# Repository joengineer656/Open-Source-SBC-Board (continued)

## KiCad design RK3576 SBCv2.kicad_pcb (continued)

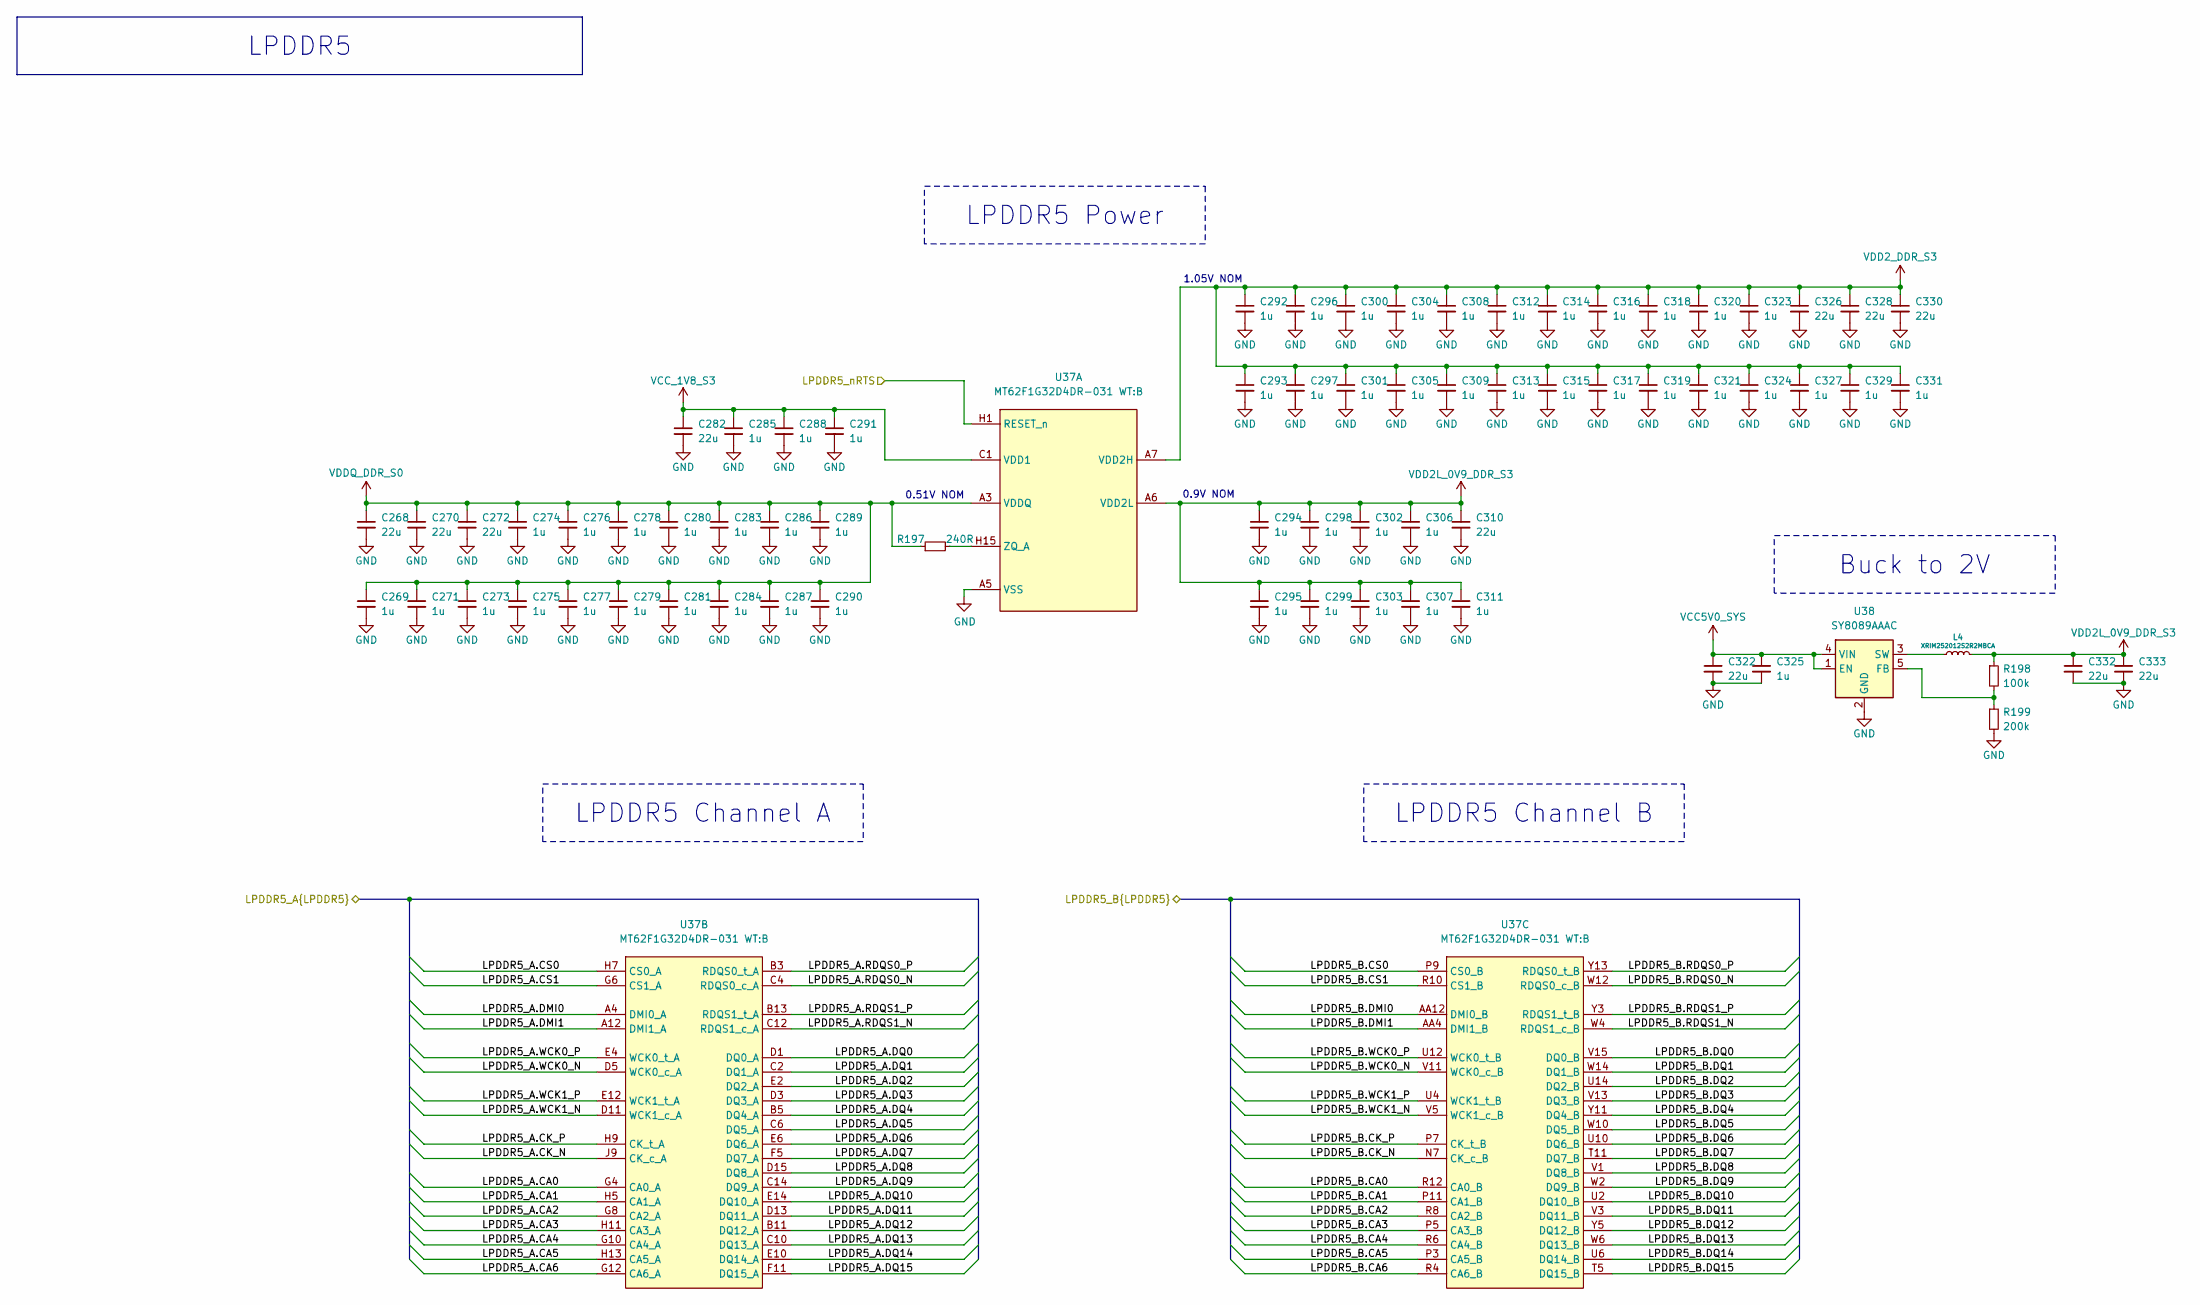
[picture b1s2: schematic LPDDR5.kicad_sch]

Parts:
C268, C270, C272, C282, C310, C322, C326, C328, C330, C332, C333: 22u; C_0603_1608Metric; Mouser Part CL10A226MP8NUNE; LCSC Part C86295
C269, C271, C273, C274, C275, C276, C277, C278, C279, C280, C281, C283, C284, C285, C286, C287, C288, C289, C290, C291, C292, C293, C294, C295, C296, C297, C298, C299, C300, C301, C302, C303, C304, C305, C306, C307, C308, C309, C311, C312, C313, C314, C315, C316, C317, C318, C319, C320, C321, C323, C324, C325, C327, C329, C331: 1u; C_0201_0603Metric_Pad0.64x0.40mm_HandSolder; Mouser Part CL03A105KP3NSNC; LCSC Part C5209398
L4: XRIM252012S2R2MBCA; L_1008_2520Metric; LCSC Part C22471111
R197: 240R; R_0402_1005Metric; Mouser Part 603-RC0402FR-07240RL; LCSC Part C114755
R198: 100k; R_0402_1005Metric; Mouser Part 603-RC0402FR-0710KL; LCSC Part C60490
R199: 200k; R_0402_1005Metric; Mouser Part 603-RC0402FR-0710KL; LCSC Part C60490
U37: MT62F1G32D4DR-031 WT:B; LPDDR5 BGA 315; MPN MT62F1G32D4DR-031 WT:B; Mouser Part 340-450481-TRAY
U38: SY8089AAAC; SOT-23-5; LCSC Part C78988

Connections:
/LPDDR5/LPDDR5_A.CA0: U37.G4 (CA0_A); also elsewhere on the board
/LPDDR5/LPDDR5_A.CA1: U37.H5 (CA1_A); also elsewhere on the board
/LPDDR5/LPDDR5_A.CA2: U37.G8 (CA2_A); also elsewhere on the board
/LPDDR5/LPDDR5_A.CA3: U37.H11 (CA3_A); also elsewhere on the board
/LPDDR5/LPDDR5_A.CA4: U37.G10 (CA4_A); also elsewhere on the board
/LPDDR5/LPDDR5_A.CA5: U37.H13 (CA5_A); also elsewhere on the board
/LPDDR5/LPDDR5_A.CA6: U37.G12 (CA6_A); also elsewhere on the board
/LPDDR5/LPDDR5_A.CK_N: U37.J9 (CK_c_A); also elsewhere on the board
/LPDDR5/LPDDR5_A.CK_P: U37.H9 (CK_t_A); also elsewhere on the board
/LPDDR5/LPDDR5_A.CS0: U37.H7 (CS0_A); also elsewhere on the board
/LPDDR5/LPDDR5_A.CS1: U37.G6 (CS1_A); also elsewhere on the board
/LPDDR5/LPDDR5_A.DMI0: U37.A4 (DMI0_A); also elsewhere on the board
/LPDDR5/LPDDR5_A.DMI1: U37.A12 (DMI1_A); also elsewhere on the board
/LPDDR5/LPDDR5_A.DQ0: U37.D1 (DQ0_A); also elsewhere on the board
/LPDDR5/LPDDR5_A.DQ1: U37.C2 (DQ1_A); also elsewhere on the board
/LPDDR5/LPDDR5_A.DQ2: U37.E2 (DQ2_A); also elsewhere on the board
/LPDDR5/LPDDR5_A.DQ3: U37.D3 (DQ3_A); also elsewhere on the board
/LPDDR5/LPDDR5_A.DQ4: U37.B5 (DQ4_A); also elsewhere on the board
/LPDDR5/LPDDR5_A.DQ5: U37.C6 (DQ5_A); also elsewhere on the board
/LPDDR5/LPDDR5_A.DQ6: U37.E6 (DQ6_A); also elsewhere on the board
/LPDDR5/LPDDR5_A.DQ7: U37.F5 (DQ7_A); also elsewhere on the board
/LPDDR5/LPDDR5_A.DQ8: U37.D15 (DQ8_A); also elsewhere on the board
/LPDDR5/LPDDR5_A.DQ9: U37.C14 (DQ9_A); also elsewhere on the board
/LPDDR5/LPDDR5_A.DQ10: U37.E14 (DQ10_A); also elsewhere on the board
/LPDDR5/LPDDR5_A.DQ11: U37.D13 (DQ11_A); also elsewhere on the board
/LPDDR5/LPDDR5_A.DQ12: U37.B11 (DQ12_A); also elsewhere on the board
/LPDDR5/LPDDR5_A.DQ13: U37.C10 (DQ13_A); also elsewhere on the board
/LPDDR5/LPDDR5_A.DQ14: U37.E10 (DQ14_A); also elsewhere on the board
/LPDDR5/LPDDR5_A.DQ15: U37.F11 (DQ15_A); also elsewhere on the board
/LPDDR5/LPDDR5_A.RDQS0_N: U37.C4 (RDQS0_c_A); also elsewhere on the board
/LPDDR5/LPDDR5_A.RDQS0_P: U37.B3 (RDQS0_t_A); also elsewhere on the board
/LPDDR5/LPDDR5_A.RDQS1_N: U37.C12 (RDQS1_c_A); also elsewhere on the board
/LPDDR5/LPDDR5_A.RDQS1_P: U37.B13 (RDQS1_t_A); also elsewhere on the board
/LPDDR5/LPDDR5_A.WCK0_N: U37.D5 (WCK0_c_A); also elsewhere on the board
/LPDDR5/LPDDR5_A.WCK0_P: U37.E4 (WCK0_t_A); also elsewhere on the board
/LPDDR5/LPDDR5_A.WCK1_N: U37.D11 (WCK1_c_A); also elsewhere on the board
/LPDDR5/LPDDR5_A.WCK1_P: U37.E12 (WCK1_t_A); also elsewhere on the board
/LPDDR5/LPDDR5_B.CA0: U37.R12 (CA0_B); also elsewhere on the board
/LPDDR5/LPDDR5_B.CA1: U37.P11 (CA1_B); also elsewhere on the board
/LPDDR5/LPDDR5_B.CA2: U37.R8 (CA2_B); also elsewhere on the board
/LPDDR5/LPDDR5_B.CA3: U37.P5 (CA3_B); also elsewhere on the board
/LPDDR5/LPDDR5_B.CA4: U37.R6 (CA4_B); also elsewhere on the board
/LPDDR5/LPDDR5_B.CA5: U37.P3 (CA5_B); also elsewhere on the board
/LPDDR5/LPDDR5_B.CA6: U37.R4 (CA6_B); also elsewhere on the board
/LPDDR5/LPDDR5_B.CK_N: U37.N7 (CK_c_B); also elsewhere on the board
/LPDDR5/LPDDR5_B.CK_P: U37.P7 (CK_t_B); also elsewhere on the board
/LPDDR5/LPDDR5_B.CS0: U37.P9 (CS0_B); also elsewhere on the board
/LPDDR5/LPDDR5_B.CS1: U37.R10 (CS1_B); also elsewhere on the board
/LPDDR5/LPDDR5_B.DMI0: U37.AA12 (DMI0_B); also elsewhere on the board
/LPDDR5/LPDDR5_B.DMI1: U37.AA4 (DMI1_B); also elsewhere on the board
/LPDDR5/LPDDR5_B.DQ0: U37.V15 (DQ0_B); also elsewhere on the board
/LPDDR5/LPDDR5_B.DQ1: U37.W14 (DQ1_B); also elsewhere on the board
/LPDDR5/LPDDR5_B.DQ2: U37.U14 (DQ2_B); also elsewhere on the board
/LPDDR5/LPDDR5_B.DQ3: U37.V13 (DQ3_B); also elsewhere on the board
/LPDDR5/LPDDR5_B.DQ4: U37.Y11 (DQ4_B); also elsewhere on the board
/LPDDR5/LPDDR5_B.DQ5: U37.W10 (DQ5_B); also elsewhere on the board
/LPDDR5/LPDDR5_B.DQ6: U37.U10 (DQ6_B); also elsewhere on the board
/LPDDR5/LPDDR5_B.DQ7: U37.T11 (DQ7_B); also elsewhere on the board
/LPDDR5/LPDDR5_B.DQ8: U37.V1 (DQ8_B); also elsewhere on the board
/LPDDR5/LPDDR5_B.DQ9: U37.W2 (DQ9_B); also elsewhere on the board
/LPDDR5/LPDDR5_B.DQ10: U37.U2 (DQ10_B); also elsewhere on the board
/LPDDR5/LPDDR5_B.DQ11: U37.V3 (DQ11_B); also elsewhere on the board
/LPDDR5/LPDDR5_B.DQ12: U37.Y5 (DQ12_B); also elsewhere on the board
/LPDDR5/LPDDR5_B.DQ13: U37.W6 (DQ13_B); also elsewhere on the board
/LPDDR5/LPDDR5_B.DQ14: U37.U6 (DQ14_B); also elsewhere on the board
/LPDDR5/LPDDR5_B.DQ15: U37.T5 (DQ15_B); also elsewhere on the board
/LPDDR5/LPDDR5_B.RDQS0_N: U37.W12 (RDQS0_c_B); also elsewhere on the board
/LPDDR5/LPDDR5_B.RDQS0_P: U37.Y13 (RDQS0_t_B); also elsewhere on the board
/LPDDR5/LPDDR5_B.RDQS1_N: U37.W4 (RDQS1_c_B); also elsewhere on the board
/LPDDR5/LPDDR5_B.RDQS1_P: U37.Y3 (RDQS1_t_B); also elsewhere on the board
/LPDDR5/LPDDR5_B.WCK0_N: U37.V11 (WCK0_c_B); also elsewhere on the board
/LPDDR5/LPDDR5_B.WCK0_P: U37.U12 (WCK0_t_B); also elsewhere on the board
/LPDDR5/LPDDR5_B.WCK1_N: U37.V5 (WCK1_c_B); also elsewhere on the board
/LPDDR5/LPDDR5_B.WCK1_P: U37.U4 (WCK1_t_B); also elsewhere on the board
/LPDDR5/LPDDR5_nRTS: U37.H1 (RESET_n); also elsewhere on the board
unnamed: L4.1, U38.3 (SW)
VDD2_DDR_S3: C292.1, C293.1, C296.1, C297.1, C300.1, C301.1, C304.1, C305.1, C308.1, C309.1, C312.1, C313.1, C314.1, C315.1, C316.1, C317.1, C318.1, C319.1, C320.1, C321.1, C323.1, C324.1, C326.1, C327.1, C328.1, C329.1, C330.1, C331.1, U37.A7 (VDD2H), U37.A8 (VDD2H), U37.A9 (VDD2H), U37.AA7 (VDD2H), U37.AA8 (VDD2H), U37.AA9 (VDD2H), U37.B7 (VDD2H), U37.B9 (VDD2H), U37.C7 (VDD2H), U37.C9 (VDD2H), U37.D8 (VDD2H), U37.E7 (VDD2H), U37.E9 (VDD2H), U37.F6 (VDD2H), U37.F7 (VDD2H), U37.F9 (VDD2H), U37.F10 (VDD2H), U37.J5 (VDD2H), U37.J11 (VDD2H), U37.K1 (VDD2H), U37.K2 (VDD2H), U37.K3 (VDD2H), U37.K4 (VDD2H), U37.K5 (VDD2H), U37.K6 (VDD2H), U37.K10 (VDD2H), U37.K11 (VDD2H), U37.K12 (VDD2H), U37.K13 (VDD2H), U37.K14 (VDD2H), U37.K15 (VDD2H), U37.L6 (VDD2H), U37.L7 (VDD2H), U37.L8 (VDD2H), U37.L9 (VDD2H), U37.L10 (VDD2H), U37.M1 (VDD2H), U37.M2 (VDD2H), U37.M3 (VDD2H), U37.M4 (VDD2H), U37.M5 (VDD2H), U37.M6 (VDD2H), U37.M10 (VDD2H), U37.M11 (VDD2H), U37.M12 (VDD2H), U37.M13 (VDD2H), U37.M14 (VDD2H), U37.M15 (VDD2H), U37.N5 (VDD2H), U37.N11 (VDD2H), U37.T6 (VDD2H), U37.T7 (VDD2H), U37.T9 (VDD2H), U37.T10 (VDD2H), U37.U7 (VDD2H), U37.U9 (VDD2H), U37.V8 (VDD2H), U37.W7 (VDD2H), U37.W9 (VDD2H), U37.Y7 (VDD2H), U37.Y9 (VDD2H); also elsewhere on the board

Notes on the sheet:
0.9V NOM
1.05V NOM
0.51V NOM
Buck to 2V
LPDDR5 Channel B
LPDDR5 Power
LPDDR5
LPDDR5 Channel A

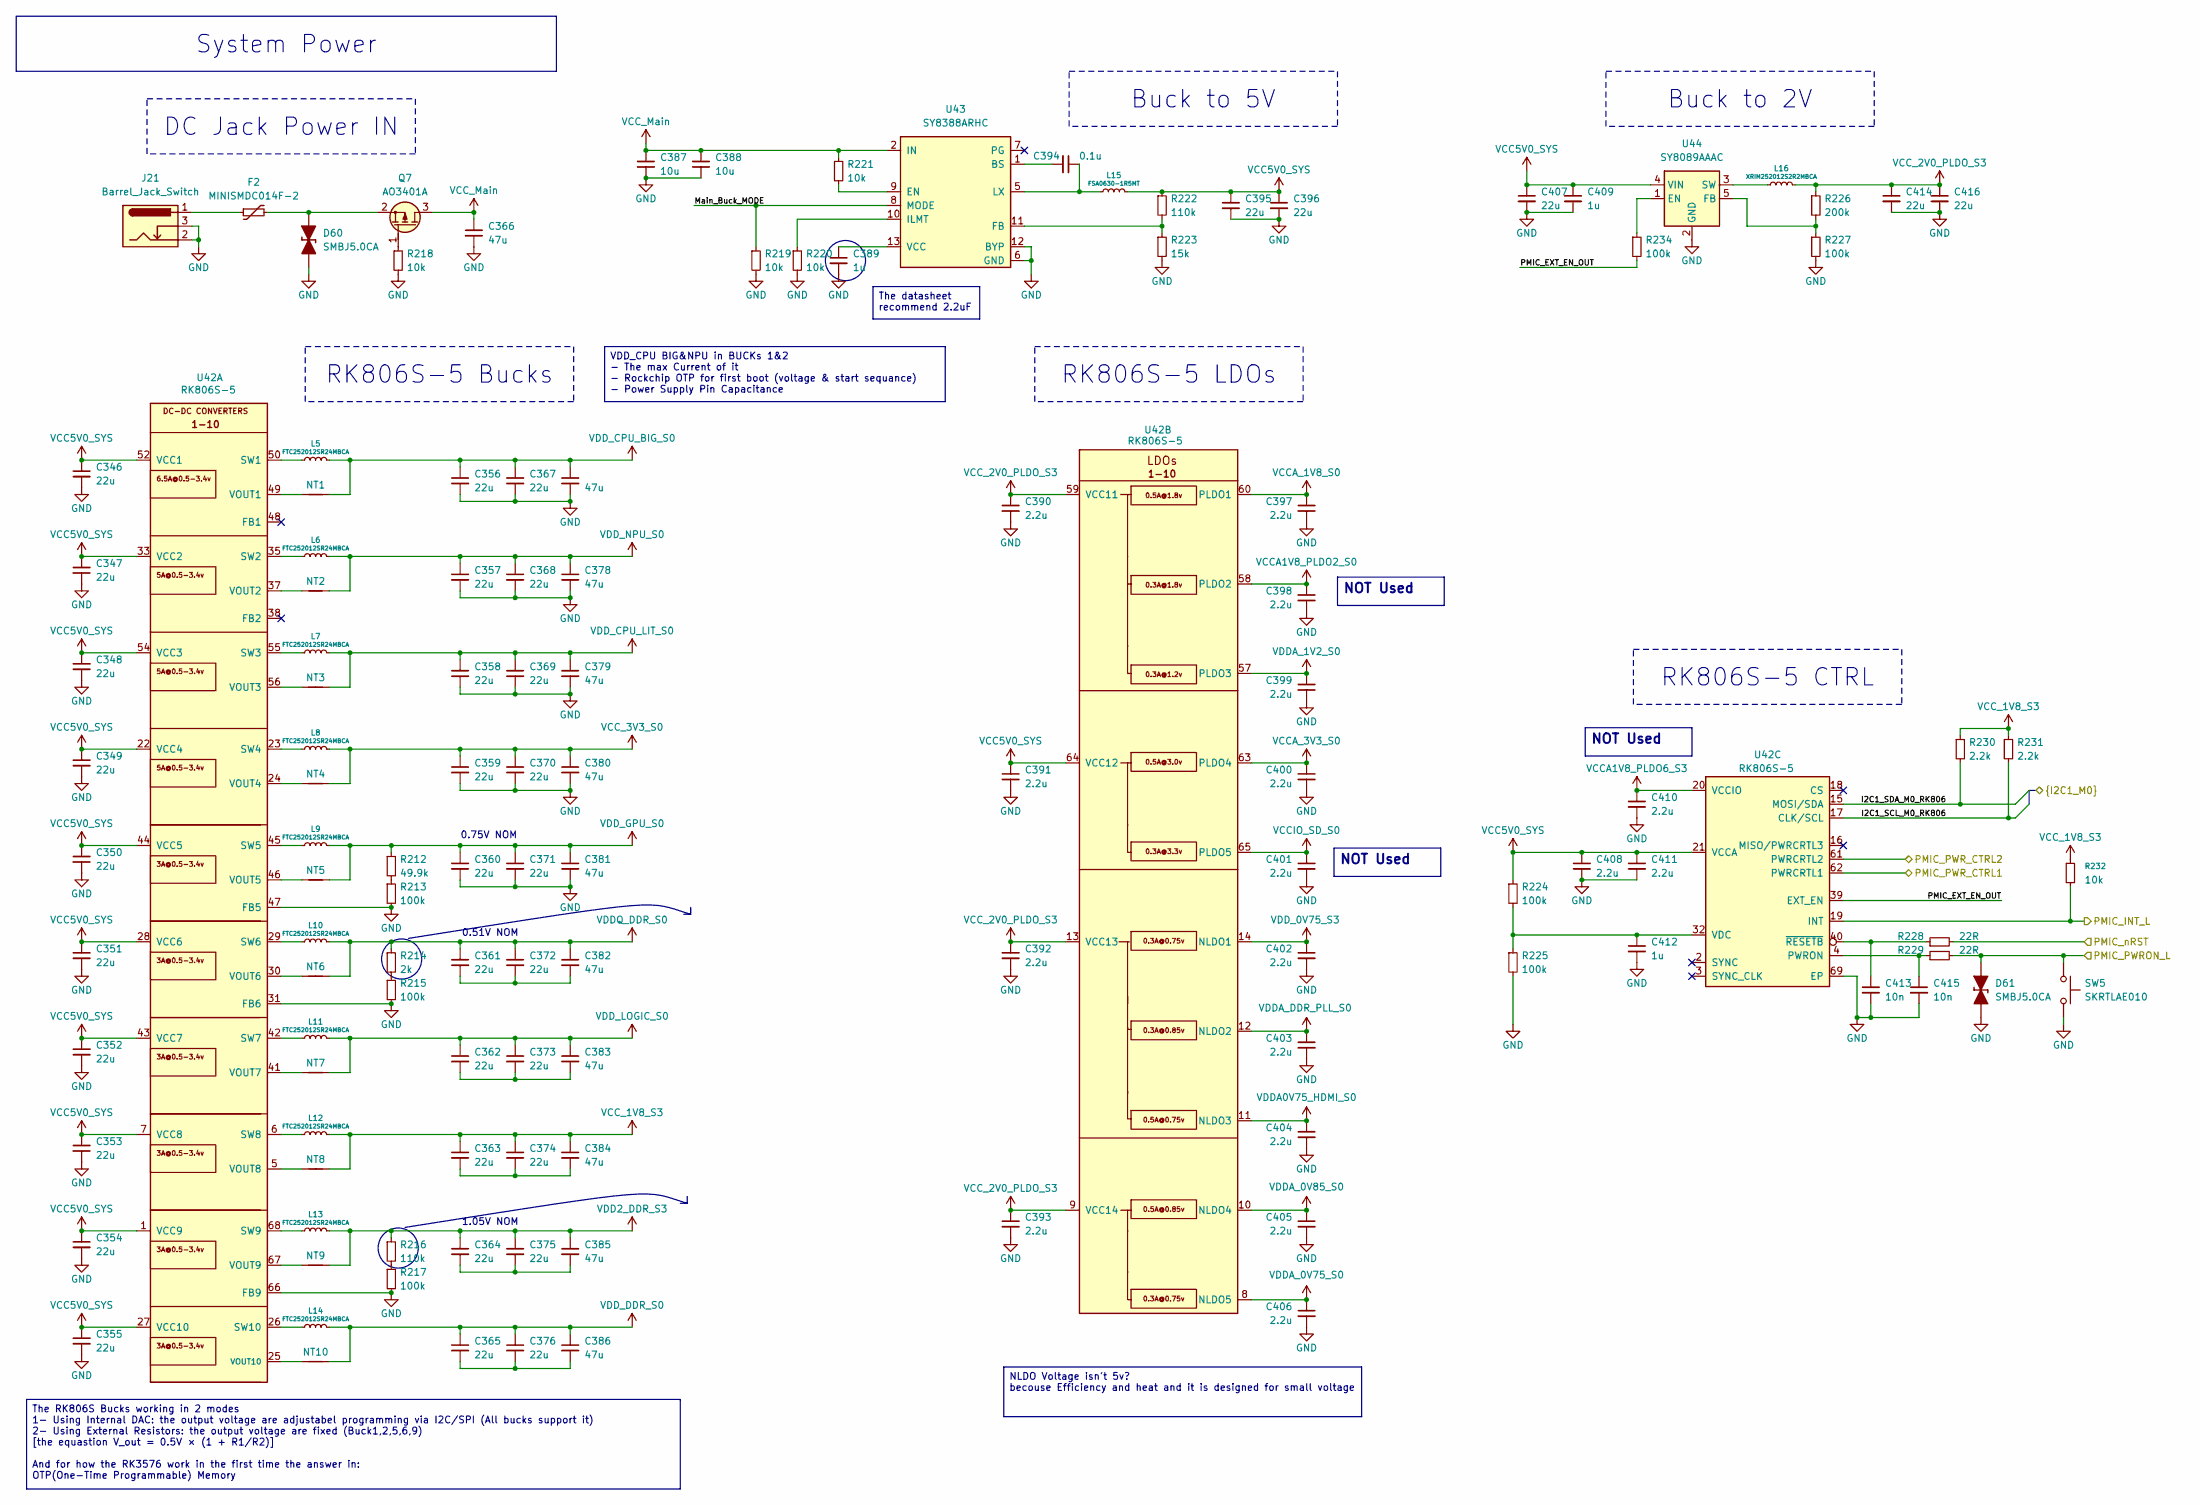
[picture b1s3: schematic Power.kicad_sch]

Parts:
C346, C347, C348, C349, C350, C351, C352, C353, C354, C355, C356, C357, C358, C359, C360, C361, C362, C363, C364, C365, C367, C368, C369, C370, C371, C372, C373, C374, C375, C376, C395, C396, C407, C414, C416: 22u; C_0603_1608Metric; Mouser Part CL10A226MP8NUNE; LCSC Part C86295
C366, C377, C378, C379, C380, C381, C382, C383, C384, C385, C386: 47u; C_0805_2012Metric; Mouser Part 187-CL21A476MQYNNNE; LCSC Part C16780
C387, C388: 10u; C_0603_1608Metric; Mouser Part 187-CL10A106KP8NNNC; LCSC Part C19702
C389, C409, C412: 1u; C_0201_0603Metric_Pad0.64x0.40mm_HandSolder; Mouser Part CL03A105KP3NSNC; LCSC Part C5209398
C390, C391, C392, C393, C397, C398, C399, C400, C401, C402, C403, C404, C405, C406, C408, C410, C411: 2.2u; C_0402_1005Metric; Mouser Part 187-CL05A225KO5NQNC; LCSC Part C170151
C394: 0.1u; C_0201_0603Metric_Pad0.64x0.40mm_HandSolder; Mouser Part 603-CC0201KRX56BB224; LCSC Part C326658
C413, C415: 10n; C_0201_0603Metric_Pad0.64x0.40mm_HandSolder; Mouser Part 187-CL03B103KP3NNNC; LCSC Part C87461
D60, D61: SMBJ5.0CA; D_SMB_TVS; Mouser Part 581-SMBJ5.0CA; LCSC Part C113975
F2: MINISMDC014F-2; Fuse_1812_4532Metric; LCSC Part C28326708
J21: Barrel_Jack_Switch; DC-JACK-TH-2.5_HC-DC-007B-2.5; LCSC Part C3010538
L5, L6, L7, L8, L9, L10, L11, L12, L13, L14: FTC252012SR24MBCA; L_1008_2520Metric; LCSC Part C5832366
L15: FSA0630-1R5MT; L_Sunlord_MWSA0603S; LCSC Part C41384300
L16: XRIM252012S2R2MBCA; L_1008_2520Metric; LCSC Part C22471111
NT1, NT2, NT3, NT4, NT5, NT6, NT7, NT8, NT9, NT10: NetTie_2; NetTie-2_SMD_Pad0.5mm
Q7: AO3401A; SOT-23; LCSC Part C347476
R212: 49.9k; R_0402_1005Metric; Mouser Part 603-RC0402FR-0749K9L; LCSC Part C137969
R213, R215, R217, R224, R225, R227, R234: 100k; R_0402_1005Metric; Mouser Part 603-RC0402FR-0710KL; LCSC Part C60490
R214: 2k; R_0402_1005Metric; Mouser Part 603AC0402FR-072KL; LCSC Part C144770
R216, R222: 110k; R_0402_1005Metric; Mouser Part 603-RC0402FR-07110KL; LCSC Part C138065
R218, R219, R220, R221, R232: 10k; R_0402_1005Metric; Mouser Part 603-RC0402FR-0710KL; LCSC Part C60490
R223: 15k; R_0402_1005Metric; Mouser Part 603-RC0402FR-0710KL; LCSC Part C60490
R226: 200k; R_0402_1005Metric; Mouser Part 603-RC0402FR-0710KL; LCSC Part C60490
R228, R229: 22R; R_0402_1005Metric; Mouser Part 603-RC0402FR-070RL; LCSC Part C106231
R230, R231: 2.2k; R_0402_1005Metric; Mouser Part 603-RC0402FR-072K2L; LCSC Part C114762
SW5: SKRTLAE010; LCSC Part C110293
U42: RK806S-5; ArtInChip_QFN-68-1EP_7x7mm_P0.35mm_EP5.49x5.49mm; LCSC Part C49174044
U43: SY8388ARHC; QFN-16-2.5x2.5-EP_SY8388ARHC; LCSC Part C5110279
U44: SY8089AAAC; SOT-23-5; LCSC Part C78988

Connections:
/Power/I2C1_SCL_M0_RK806: R231.2, U42.17 (CLK/SCL); also elsewhere on the board
/Power/I2C1_SDA_M0_RK806: R230.2, U42.15 (MOSI/SDA); also elsewhere on the board
/Power/Main_Buck_MODE: R219.1, U43.8 (MODE)
/Power/PMIC_EXT_EN_OUT: R234.2, U42.39 (EXT_EN)
/Power/PMIC_INT_L: R232.2, U42.19 (INT); also elsewhere on the board
/Power/PMIC_PWRON_L: D61.2 (A), R229.2, SW5.1; also elsewhere on the board
/Power/PMIC_PWR_CTRL1: U42.62 (PWRCRTL1); also elsewhere on the board
/Power/PMIC_PWR_CTRL2: U42.61 (PWRCRTL2); also elsewhere on the board
/Power/PMIC_nRST: R228.2; also elsewhere on the board
unnamed: C361.2, C372.2, C382.2
unnamed: C362.2, C373.2, C383.2
unnamed: C363.2, C374.2, C384.2
unnamed: C364.2, C375.2, C385.2
unnamed: C365.2, C376.2, C386.2
unnamed: C394.1, L15.1, U43.5 (LX), U43.15 (LX), U43.16 (LX)
unnamed: D60.2 (A), F2.2, Q7.2 (S)
unnamed: F2.1, J21.1
unnamed: L5.1, U42.50 (SW1), U42.51 (SW1)
unnamed: L6.1, U42.35 (SW2), U42.36 (SW2)
unnamed: Q7.1 (G), R218.1
unnamed: R212.2, R213.1
unnamed: R214.2, R215.1
unnamed: R216.2, R217.1
unnamed: L7.1, U42.55 (SW3)
unnamed: L8.1, U42.23 (SW4)
unnamed: L9.1, U42.45 (SW5)
unnamed: L10.1, U42.29 (SW6)
unnamed: L11.1, U42.42 (SW7)
unnamed: L12.1, U42.6 (SW8)
unnamed: L13.1, U42.68 (SW9)
unnamed: L14.1, U42.26 (SW10)
unnamed: NT1.1, U42.49 (VOUT1)
unnamed: NT2.1, U42.37 (VOUT2)
unnamed: NT3.1, U42.56 (VOUT3)
unnamed: NT4.1, U42.24 (VOUT4)
unnamed: NT5.1, U42.46 (VOUT5)
unnamed: NT6.1, U42.30 (VOUT6)
unnamed: NT7.1, U42.41 (VOUT7)
unnamed: NT8.1, U42.5 (VOUT8)
unnamed: NT9.1, U42.67 (VOUT9)
unnamed: NT10.1, U42.25 (VOUT10)
unnamed: C415.1, R229.1, U42.4 (PWRON)
unnamed: C412.1, R224.2, R225.1, U42.32 (VDC)
unnamed: C413.1, R228.1, U42.40 (~RESETB)
unnamed: C394.2, U43.1 (BS)
unnamed: R221.2, U43.9 (EN)
unnamed: R222.2, R223.1, U43.11 (FB)
unnamed: R220.1, U43.10 (ILMT)
unnamed: C389.1, U43.13 (VCC)
unnamed: R234.1, U44.1 (EN)
unnamed: R226.2, R227.1, U44.5 (FB)
unnamed: L16.1, U44.3 (SW)
VCCA1V8_PLDO2_S0: C398.1, U42.58 (PLDO2)
VCCA1V8_PLDO6_S3: C410.1, U42.20 (VCCIO)
VCCIO_SD_S0: C401.1, U42.65 (PLDO5)
VDD2_DDR_S3: C364.1, C375.1, C385.1, L13.2, NT9.2, R216.1; also elsewhere on the board
VDDA0V75_HDMI_S0: C404.1, U42.11 (NLDO3); also elsewhere on the board
VDDA_0V75_S0: C406.1, U42.8 (NLDO5); also elsewhere on the board
VDDA_0V85_S0: C405.1, U42.10 (NLDO4); also elsewhere on the board
VDDA_1V2_S0: C399.1, U42.57 (PLDO3); also elsewhere on the board
VDDA_DDR_PLL_S0: C403.1, U42.12 (NLDO2); also elsewhere on the board
VDD_0V75_S3: C402.1, U42.14 (NLDO1)
VDD_CPU_BIG_S0: C356.1, C367.1, C377.1, L5.2, NT1.2; also elsewhere on the board
VDD_CPU_LIT_S0: C358.1, C369.1, C379.1, L7.2, NT3.2; also elsewhere on the board
VDD_DDR_S0: C365.1, C376.1, C386.1, L14.2, NT10.2; also elsewhere on the board
VDD_GPU_S0: C360.1, C371.1, C381.1, L9.2, NT5.2, R212.1; also elsewhere on the board
VDD_LOGIC_S0: C362.1, C373.1, C383.1, L11.2, NT7.2; also elsewhere on the board
VDD_NPU_S0: C357.1, C368.1, C378.1, L6.2, NT2.2; also elsewhere on the board

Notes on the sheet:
1.05V NOM
0.51V NOM
0.75V NOM
VDD_CPU BIG&NPU in BUCKs 1&2 - The max Current of it - Rockchip OTP for first boot (voltage & start sequance) - Power Supply Pin Capacitance
RK806S-5 LDOs
The datasheet recommend 2.2uF
NLDO Voltage isn't 5v? becouse Efficiency and heat and it is designed for small voltage
The RK806S Bucks working in 2 modes 1- Using Internal DAC: the output voltage are adjustabel programming via I2C/SPI (All bucks support it) 2- Using External Resistors: the output voltage are fixed (Buck1,2,5,6,9) [the equastion V_out = 0.5V × (1 + R1/R2)] And for how the RK3576 work in the first t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
Buck to 2V
RK806S-5 Bucks
System Power
NOT Used
DC Jack Power IN
RK806S-5 CTRL
Buck to 5V
